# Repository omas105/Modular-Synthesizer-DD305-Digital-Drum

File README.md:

# Modular-Synthesizer-DD305-Digital-Drum
Circuit bending a DD305 digital drum machine into a synthesizer module
##

[Schematic](DD305%20Digital%20Drum%20Synth/DD305%20Digital%20Drum%20Synth.pdf)

[Drum voice list](Drum_voices.pdf)

##
<p>
  </a>
</p>

## License

[GNU General Public License (GPLv3)](LICENSE)

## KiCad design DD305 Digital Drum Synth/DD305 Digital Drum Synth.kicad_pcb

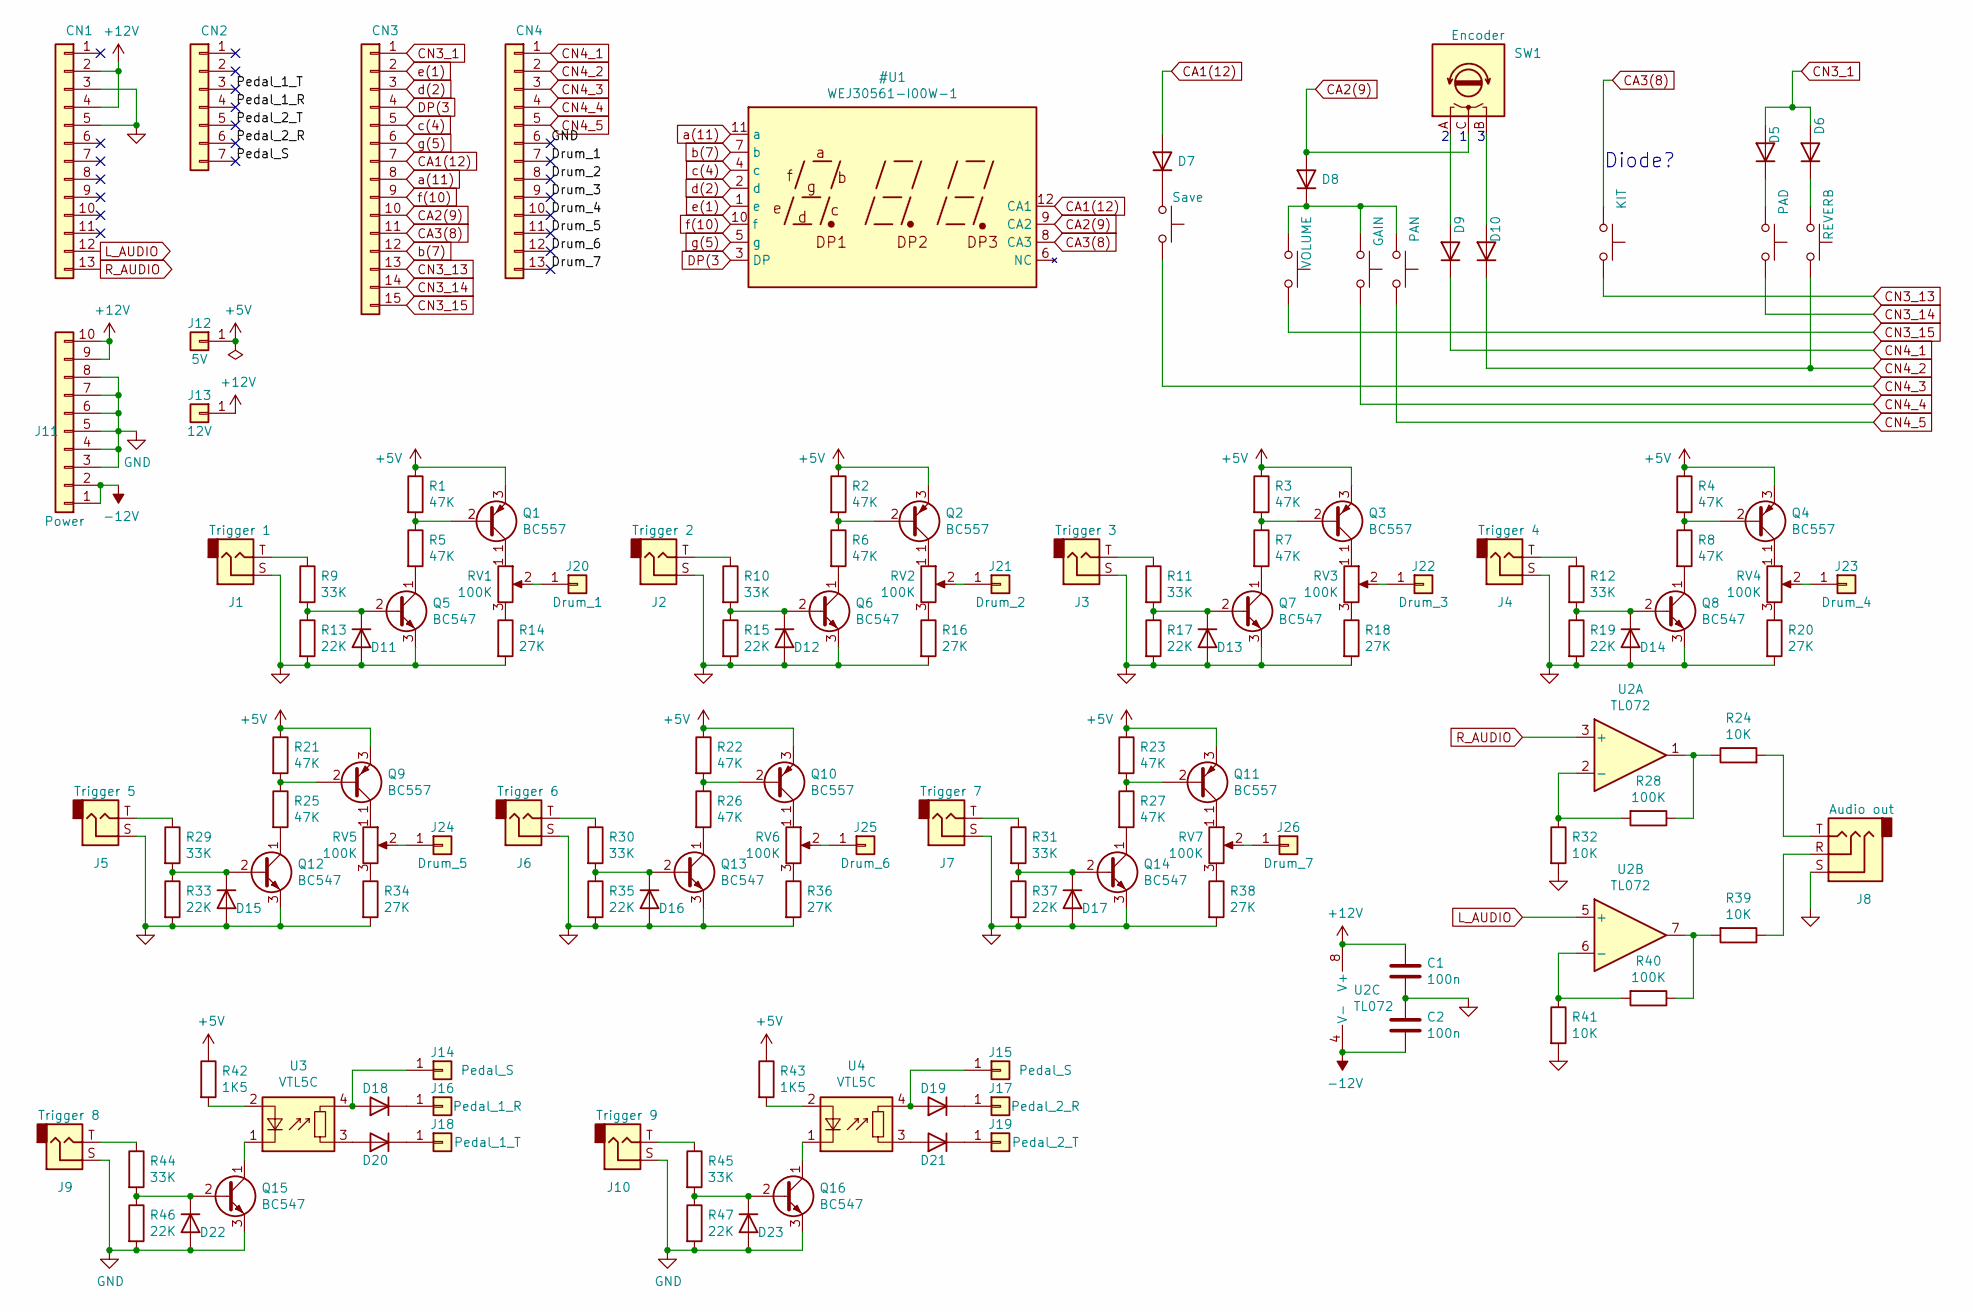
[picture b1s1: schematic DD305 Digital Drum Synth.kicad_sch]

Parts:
C1, C2: 100n; C_Disc_D5.0mm_W2.5mm_P5.00mm
D5, D6, D7, D8, D9, D10, D11, D12, D13, D14, D15, D16, D17, D22, D23: 1N4148; D_DO-35_SOD27_P10.16mm_Horizontal
D18, D19, D20, D21: 1N4148; D_DO-35_SOD27_P7.62mm_Horizontal
J1: Trigger 1; Jack_PinHeader_1x02_P2.54mm_Vertical
J2: Trigger 2; Jack_PinHeader_1x02_P2.54mm_Vertical
J3: Trigger 3; Jack_PinHeader_1x02_P2.54mm_Vertical
J4: Trigger 4; Jack_PinHeader_1x02_P2.54mm_Vertical
J5: Trigger 5; Jack_PinHeader_1x02_P2.54mm_Vertical
J6: Trigger 6; Jack_PinHeader_1x02_P2.54mm_Vertical
J7: Trigger 7; Jack_PinHeader_1x02_P2.54mm_Vertical
J8: Audio out; Jack_6.35mm_Neutrik_NMJ6HFD2_Horizontal
J9: Trigger 8; Jack_PinHeader_1x02_P2.54mm_Vertical
J10: Trigger 9; Jack_PinHeader_1x02_P2.54mm_Vertical
J11: Power; IDC-Header_2x05_P2.54mm_Vertical
J12: 5V; PinHeader_1x01_P2.54mm_Vertical
J13: 12V; PinHeader_1x01_P2.54mm_Vertical
J14, J15: Pedal_S; PinHeader_1x01_P2.54mm_Vertical
J16: Pedal_1_R; PinHeader_1x01_P2.54mm_Vertical
J17: Pedal_2_R; PinHeader_1x01_P2.54mm_Vertical
J18: Pedal_1_T; PinHeader_1x01_P2.54mm_Vertical
J19: Pedal_2_T; PinHeader_1x01_P2.54mm_Vertical
J20: Drum_1; PinHeader_1x01_P2.54mm_Vertical
J21: Drum_2; PinHeader_1x01_P2.54mm_Vertical
J22: Drum_3; PinHeader_1x01_P2.54mm_Vertical
J23: Drum_4; PinHeader_1x01_P2.54mm_Vertical
J24: Drum_5; PinHeader_1x01_P2.54mm_Vertical
J25: Drum_6; PinHeader_1x01_P2.54mm_Vertical
J26: Drum_7; PinHeader_1x01_P2.54mm_Vertical
Q1, Q2, Q3, Q4, Q9, Q10, Q11: BC557; TO-92_Inline_Wide_Longpads
Q5, Q6, Q7, Q8, Q12, Q13, Q14, Q15, Q16: BC547; TO-92_Inline_Wide_Longpads
R1, R2, R3, R4, R5, R6, R7, R8, R21, R22, R23, R25, R26, R27: 47K; R_Axial_DIN0207_L6.3mm_D2.5mm_P10.16mm_Horizontal
R9, R10, R11, R12, R29, R30, R31, R44, R45: 33K; R_Axial_DIN0207_L6.3mm_D2.5mm_P7.62mm_Horizontal
R13, R15, R17, R19, R33, R35, R37, R46, R47: 22K; R_Axial_DIN0207_L6.3mm_D2.5mm_P10.16mm_Horizontal
R14, R16, R18, R20, R34, R36, R38: 27K; R_Axial_DIN0207_L6.3mm_D2.5mm_P10.16mm_Horizontal
R24, R32, R39, R41: 10K; R_Axial_DIN0207_L6.3mm_D2.5mm_P10.16mm_Horizontal
R28, R40: 100K; R_Axial_DIN0207_L6.3mm_D2.5mm_P10.16mm_Horizontal
R42, R43: 1K5; R_Axial_DIN0207_L6.3mm_D2.5mm_P10.16mm_Horizontal
RV1, RV2, RV3, RV4, RV5, RV6, RV7: 100K; PinHeader_1x03_P2.54mm_Vertical
SW1: Encoder; RotaryEncoder_Alps_EC12E_Vertical_H20mm_CircularMountingHol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
SW2: Save; PinHeader_1x02_P2.54mm_Vertical
SW3: KIT; PinHeader_1x02_P2.54mm_Vertical
SW4: PAD; PinHeader_1x02_P2.54mm_Vertical
SW5: REVERB; PinHeader_1x02_P2.54mm_Vertical
SW6: VOLUME; PinHeader_1x02_P2.54mm_Vertical
SW7: GAIN; PinHeader_1x02_P2.54mm_Vertical
SW8: PAN; PinHeader_1x02_P2.54mm_Vertical
U2: TL072; DIP-8_W7.62mm_Socket_LongPads
U3, U4: VTL5C; Vactrol

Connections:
+5V: J12.1, Q1.3 (E), Q2.3 (E), Q3.3 (E), Q4.3 (E), Q9.3 (E), Q10.3 (E), Q11.3 (E), R1.1, R2.1, R3.1, R4.1, R21.1, R22.1, R23.1, R42.1, R43.1
-12V: C2.2, J11.1, J11.2, U2.4 (V-)
unnamed: D5.1 (K), SW4.1
unnamed: D6.1 (K), SW5.1
unnamed: D7.1 (K), SW2.1
unnamed: D8.1 (K), SW6.1, SW7.1, SW8.1
unnamed: D9.2 (A), SW1.A
unnamed: D10.2 (A), SW1.B
unnamed: D11.1 (K), Q5.2 (B), R9.2, R13.1
unnamed: D12.1 (K), Q6.2 (B), R10.2, R15.1
unnamed: D13.1 (K), Q7.2 (B), R11.2, R17.1
unnamed: D14.1 (K), Q8.2 (B), R12.2, R19.1
unnamed: D15.1 (K), Q12.2 (B), R29.2, R33.1
unnamed: D16.1 (K), Q13.2 (B), R30.2, R35.1
unnamed: D17.1 (K), Q14.2 (B), R31.2, R37.1
unnamed: D18.1 (K), J16.1
unnamed: D18.2 (A), J14.1, U3.4
unnamed: D19.1 (K), J17.1
unnamed: D19.2 (A), J15.1, U4.4
unnamed: D20.1 (K), J18.1
unnamed: D20.2 (A), U3.3
unnamed: D21.1 (K), J19.1
unnamed: D21.2 (A), U4.3
unnamed: D22.1 (K), Q15.2 (B), R44.2, R46.1
unnamed: D23.1 (K), Q16.2 (B), R45.2, R47.1
unnamed: J1.T, R9.1
unnamed: J2.T, R10.1
unnamed: J3.T, R11.1
unnamed: J4.T, R12.1
unnamed: J5.T, R29.1
unnamed: J6.T, R30.1
unnamed: J7.T, R31.1
unnamed: J8.R, R39.1
unnamed: J8.T, R24.2
unnamed: J9.T, R44.1
unnamed: J10.T, R45.1
unnamed: J20.1, RV1.2
unnamed: J21.1, RV2.2
unnamed: J22.1, RV3.2
unnamed: J23.1, RV4.2
unnamed: J24.1, RV5.2
unnamed: J25.1, RV6.2
unnamed: J26.1, RV7.2
unnamed: Q1.1 (C), RV1.1
unnamed: Q1.2 (B), R1.2, R5.1
unnamed: Q2.1 (C), RV2.1
unnamed: Q2.2 (B), R2.2, R6.1
unnamed: Q3.1 (C), RV3.1
unnamed: Q3.2 (B), R3.2, R7.1
unnamed: Q4.1 (C), RV4.1
unnamed: Q4.2 (B), R4.2, R8.1
unnamed: Q5.1 (C), R5.2
unnamed: Q6.1 (C), R6.2
unnamed: Q7.1 (C), R7.2
unnamed: Q8.1 (C), R8.2
unnamed: Q9.1 (C), RV5.1
unnamed: Q9.2 (B), R21.2, R25.1
unnamed: Q10.1 (C), RV6.1
unnamed: Q10.2 (B), R22.2, R26.1
unnamed: Q11.1 (C), RV7.1
unnamed: Q11.2 (B), R23.2, R27.1
unnamed: Q12.1 (C), R25.2
unnamed: Q13.1 (C), R26.2
unnamed: Q14.1 (C), R27.2
unnamed: Q15.1 (C), U3.1 (-)
unnamed: Q16.1 (C), U4.1 (-)
unnamed: R14.1, RV1.3
unnamed: R16.1, RV2.3
unnamed: R18.1, RV3.3
unnamed: R20.1, RV4.3
unnamed: R24.1, R28.1, U2.1
unnamed: R28.2, R32.1, U2.2 (-)
unnamed: R34.1, RV5.3
unnamed: R36.1, RV6.3
unnamed: R38.1, RV7.3
unnamed: R39.2, R40.1, U2.7
unnamed: R40.2, R41.1, U2.6 (-)
unnamed: R42.2, U3.2 (+)
unnamed: R43.2, U4.2 (+)

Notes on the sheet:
Diode?

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
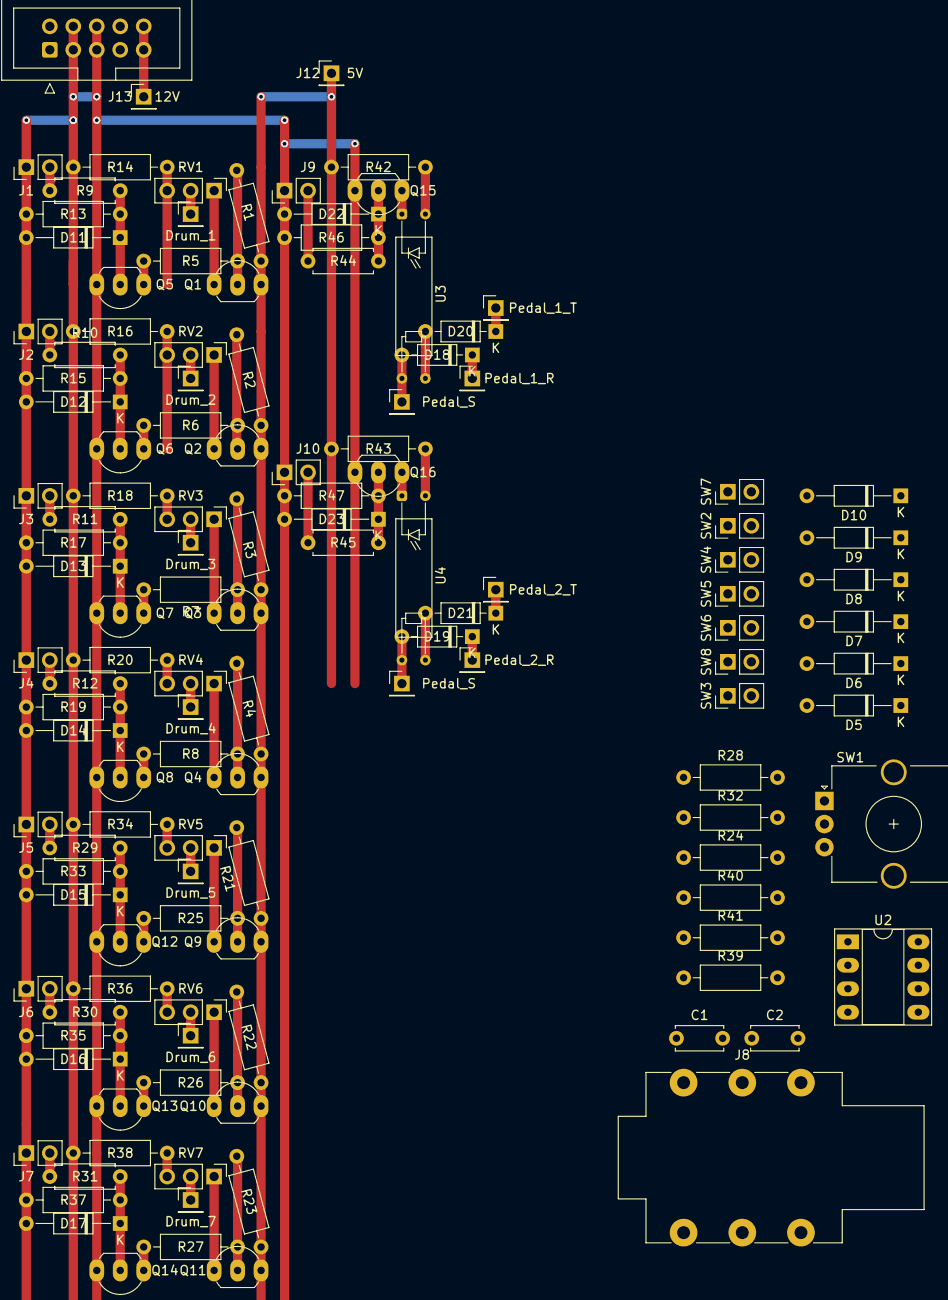
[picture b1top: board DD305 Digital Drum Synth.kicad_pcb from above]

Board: 2 copper layers, 128 parts (0 on the bottom side), 84 nets.

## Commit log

2023-06-30 init commit
